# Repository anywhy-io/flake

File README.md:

<div align="center">
    
    <h3>Anywhy Flake</h3>
    <p><i>be productive, stay healthy and enjoy the process.</i></p>
</div>

# Why

By the 19th century, a need for a faster way of writing had emerged, which led to the invention of typewriters. Two centuries later, modern keyboards don't look much different from their predecessors, even though such design has been proven to be quite inefficient and often harmful.

Addressing these problems leads to huge benefits considering how often people use keyboards in the modern world.

# How

## Split

Regular keyboards are made in a single monolithic block, and the main problem is that such a form factor requires our forearms to meet in the center. To compensate for this, wrists are bent apart. This position creates an unnatural angle between the forearm and the wrist, which in the long term will likely lead to constant wrist pain.

Each half of the split keyboard can be rotated and placed in any suitable way so everyone can adapt the setup to their personal preference, avoiding potential damage to the wrists. As a bonus, we get free space right between the halves which can be occupied by a trackpad, coffee, or even a cat =^..^=

## Stagger

If you take your hand and look at the fingers, you can notice that they are positioned horizontally. Now take a look at your keyboard - the keys are grouped in arrays that are shifted vertically, known as row-based stagger.

This well-known layout forces your fingers to move in a counterintuitive way. The solution to that problem is simple: we need to rearrange the keys in a more human-friendly way.

As you can see, Flake has what's called a column-based stagger. Because of this, keys are located in the path of natural finger movement, which results in a much more pleasant typing experience and reduced fatigue.

## Key switches

There are a huge amount of various keyboard switches with different feel, size, sound, height and so on. Such variety is awesome, but the problem arrives when you have to chose one.

To address this issue, Flake utilizes hot-swap sockets. There are two different sockets per key, allowing you to use any Cherry MX and low-profile Kailh Choc switches. This way, you can always experiment with the look and feel of the keyboard and change it according to your mood.

## Keys amount

There's a high chance that some might feel confused seeing such a small number of keys, considering user productivity is one of the priorities for Anywhy.

Indeed, Flake has fewer keys than most conventional keyboards, and that's not a compromise, but a feature. A large number of keys causes hands to move around to reach further-placed keys.

Having fewer keys doesn't mean less functionality. In fact, Flake is not only fully input-compatible with regular keyboards but also allows you to add more keys than most keyboards have. All thanks to [ZMK Firmware](https://zmk.dev) and its features such as [layers](https://zmk.dev/docs/keymaps#layers).

### Flake L

There's a Flake L with 58 keys for those who aren't ready to jump down the rabbit hole yet or just prefer more keys.

### Flake S

For people who strive for absolute comfort and compactness, there is also Flake S with 40 keys.

## Thickness

The keyboard has been designed to be as thin as possible while maintaining a sturdy construction.

The keyboard body is only ~0.8 cm (without feet), which combined with the low-profile switches and caps, greatly enhances comfort.

# What

Flake supports both wired and wireless (Bluetooth) connection, which makes it perfect for both home usage with a PC or portable setup with a laptop, tablet, or even smartphone.

To achieve both types of connectivity, each half has two USB-C ports, one on the top and one on the inner side. The side port is used to connect the halves together, and then one of them (usually the left one) can be connected to any device using the top port, which is also used to charge the keyboard.

> Ports on the side are used only to communicate with each other, so they can't be used to charge the keyboard or to flash the new firmware

The keyboard allows for a maximum battery capacity of 200mah. On a single charge, the left half will last ~1 month and the right half will last over 4 months when used for 6 hours every day.

> The calculations are done with the nice!nano controller.

In order to use MX Switches, the special "plate" comes with the Flake which should be placed between the board and the switches.

# Build

If you want to build the keyboard yourself, check out [Guide](./docs/build_guide.md), which describes everything you need to build your own Flake. 

Also, make sure to check out the [Gallery ✨](./docs/gallery.md) with awesome Flake builds.

# Credits

Huge thanks to:

- [@foostan](https://github.com/foostan), the author of [Corne Keyboard](https://github.com/foostan/crkbd) which was my introduction to the world of ergonomic keyboards.
  
- [@pashutk](https://github.com/pashutk), the author of [Chocofi](https://github.com/pashutk/chocofi), an amazing tiny keyboard I've been using for a while.
  
- [@ebastler](https://github.com/ebastler/) for his amazing [marbastlib](https://github.com/ebastler/marbastlib) which is being used as the basis for footprint switches

- [@josefadamcik](https://github.com/josefadamcik), the author of [Sofle](https://github.com/josefadamcik/SofleKeyboard) which gave huge inspiration for the Flake's key layout.
  
- [@petejohanson](https://github.com/petejohanson) for creating [ZMK Firmware](https://github.com/zmkfirmware/zmk) and all the [contributors](https://github.com/zmkfirmware/zmk/graphs/contributors) that make it better each day.

- Everyone working on [KiCad](https://gitlab.com/kicad/code/kicad) and [FreeCAD](https://github.com/FreeCAD/FreeCAD), for creating such powerful open source tools

- People from the [ZMK discord server](https://zmk.dev/community/discord/invite) for being so kind while helping me learn how to design PCB and how to debug and solve various problems.

- Finally, thank you to everyone who explores unpopular technologies, digs into niche topics, and makes amazing things possible.

## Stars

Your stars give motivation to keep improving the project :)

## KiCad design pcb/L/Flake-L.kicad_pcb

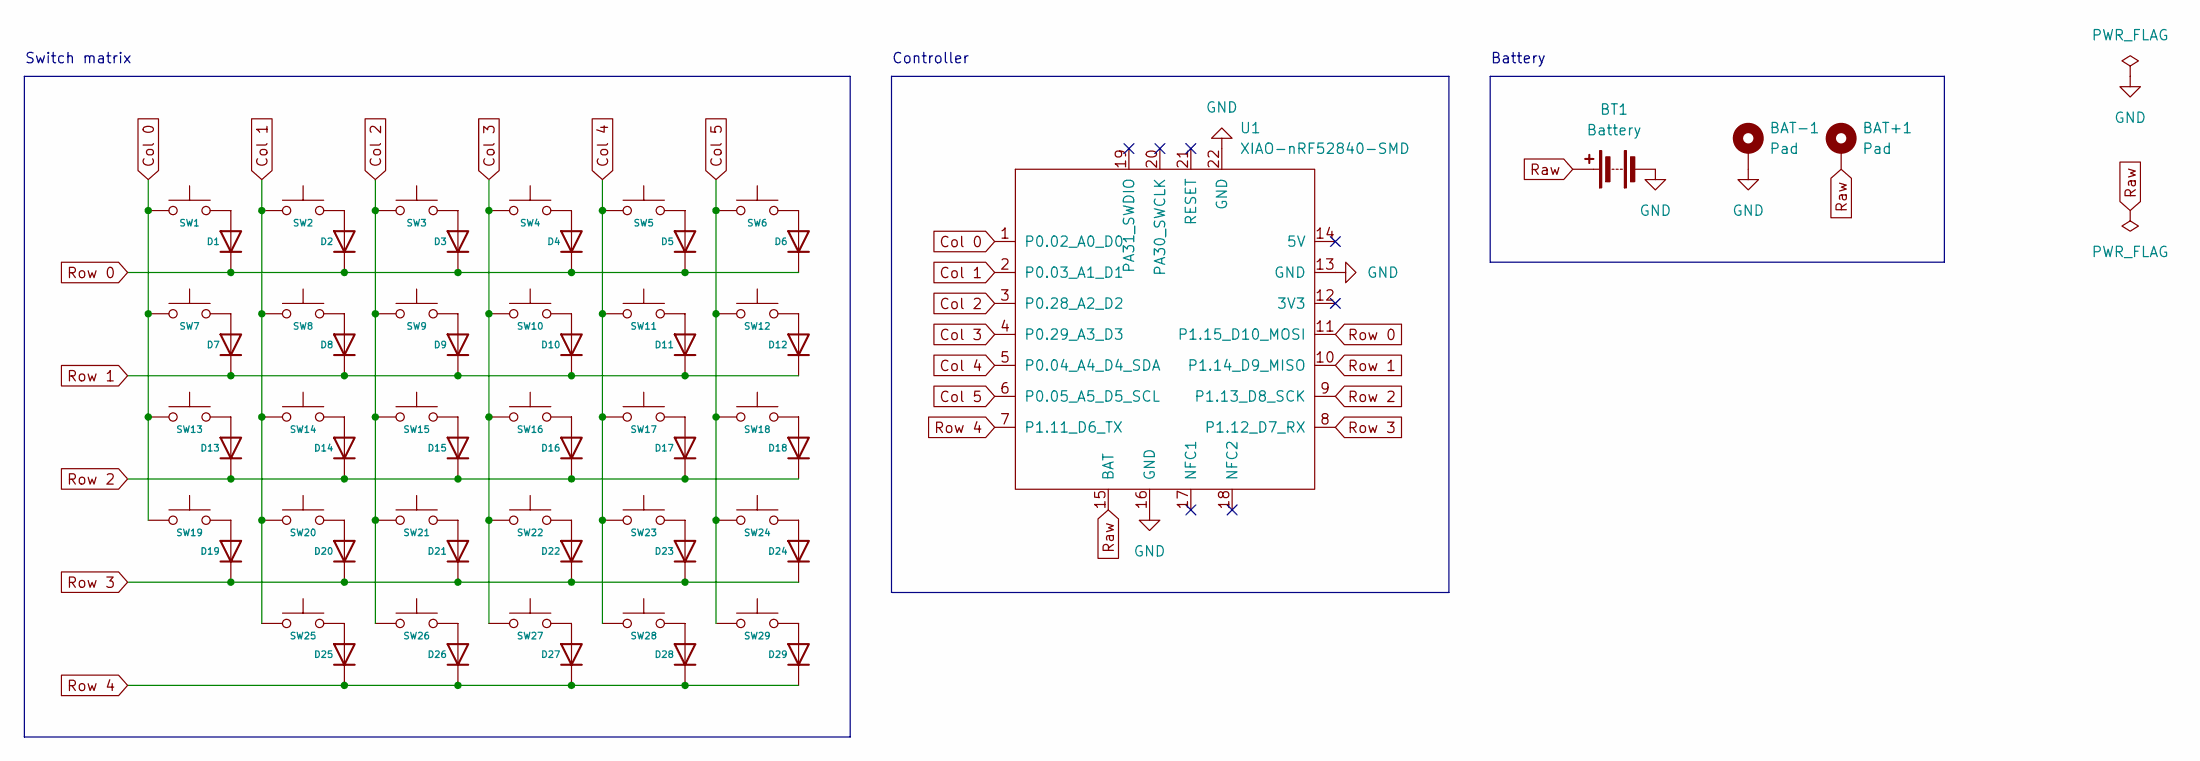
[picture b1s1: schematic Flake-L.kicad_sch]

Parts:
BAT+1: Pad
BAT-1: Pad
BT1: Battery; JST_1.25mm_Reversible
D1, D2, D3, D4, D5, D6, D7, D8, D9, D10, D11, D12, D13, D14, D15, D16, D17, D18, D19, D20, D21, D22, D23, D24, D25, D26, D27, D28, D29: D; D_SOD-123_HandSoldering_Reversible
SW1, SW2, SW3, SW4, SW5, SW6, SW7, SW8, SW9, SW10, SW11, SW12, SW13, SW14, SW15, SW16, SW17, SW18, SW19, SW20, SW21, SW22, SW23, SW24, SW25, SW26, SW27, SW28, SW29: SW_Push; SW_MX_Choc_Hotswap_Reversible
U1: XIAO-nRF52840-SMD

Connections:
Col 0: SW1.1, SW7.1, SW13.1, SW19.1, U1.1 (P0.02_A0_D0)
Col 1: SW2.1, SW8.1, SW14.1, SW20.1, SW25.1, U1.2 (P0.03_A1_D1)
Col 2: SW3.1, SW9.1, SW15.1, SW21.1, SW26.1, U1.3 (P0.28_A2_D2)
Col 3: SW4.1, SW10.1, SW16.1, SW22.1, SW27.1, U1.4 (P0.29_A3_D3)
Col 4: SW5.1, SW11.1, SW17.1, SW23.1, SW28.1, U1.5 (P0.04_A4_D4_SDA)
Col 5: SW6.1, SW12.1, SW18.1, SW24.1, SW29.1, U1.6 (P0.05_A5_D5_SCL)
GND: BAT-1.1, BT1.2 (-), U1.13 (GND), U1.16 (GND), U1.22 (GND)
unnamed: D1.2 (A), SW1.2
unnamed: D2.2 (A), SW2.2
unnamed: D3.2 (A), SW3.2
unnamed: D4.2 (A), SW4.2
unnamed: D5.2 (A), SW5.2
unnamed: D6.2 (A), SW6.2
unnamed: D7.2 (A), SW7.2
unnamed: D8.2 (A), SW8.2
unnamed: D9.2 (A), SW9.2
unnamed: D10.2 (A), SW10.2
unnamed: D11.2 (A), SW11.2
unnamed: D12.2 (A), SW12.2
unnamed: D13.2 (A), SW13.2
unnamed: D14.2 (A), SW14.2
unnamed: D15.2 (A), SW15.2
unnamed: D16.2 (A), SW16.2
unnamed: D17.2 (A), SW17.2
unnamed: D18.2 (A), SW18.2
unnamed: D19.2 (A), SW19.2
unnamed: D20.2 (A), SW20.2
unnamed: D21.2 (A), SW21.2
unnamed: D22.2 (A), SW22.2
unnamed: D23.2 (A), SW23.2
unnamed: D24.2 (A), SW24.2
unnamed: D25.2 (A), SW25.2
unnamed: D26.2 (A), SW26.2
unnamed: D27.2 (A), SW27.2
unnamed: D28.2 (A), SW28.2
unnamed: D29.2 (A), SW29.2
Raw: BAT+1.1, BT1.1 (+), U1.15 (BAT)
Row 0: D1.1 (K), D2.1 (K), D3.1 (K), D4.1 (K), D5.1 (K), D6.1 (K), U1.11 (P1.15_D10_MOSI)
Row 1: D7.1 (K), D8.1 (K), D9.1 (K), D10.1 (K), D11.1 (K), D12.1 (K), U1.10 (P1.14_D9_MISO)
Row 2: D13.1 (K), D14.1 (K), D15.1 (K), D16.1 (K), D17.1 (K), D18.1 (K), U1.9 (P1.13_D8_SCK)
Row 3: D19.1 (K), D20.1 (K), D21.1 (K), D22.1 (K), D23.1 (K), D24.1 (K), U1.8 (P1.12_D7_RX)
Row 4: D25.1 (K), D26.1 (K), D27.1 (K), D28.1 (K), D29.1 (K), U1.7 (P1.11_D6_TX)

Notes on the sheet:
Switch matrix
Controller
Battery

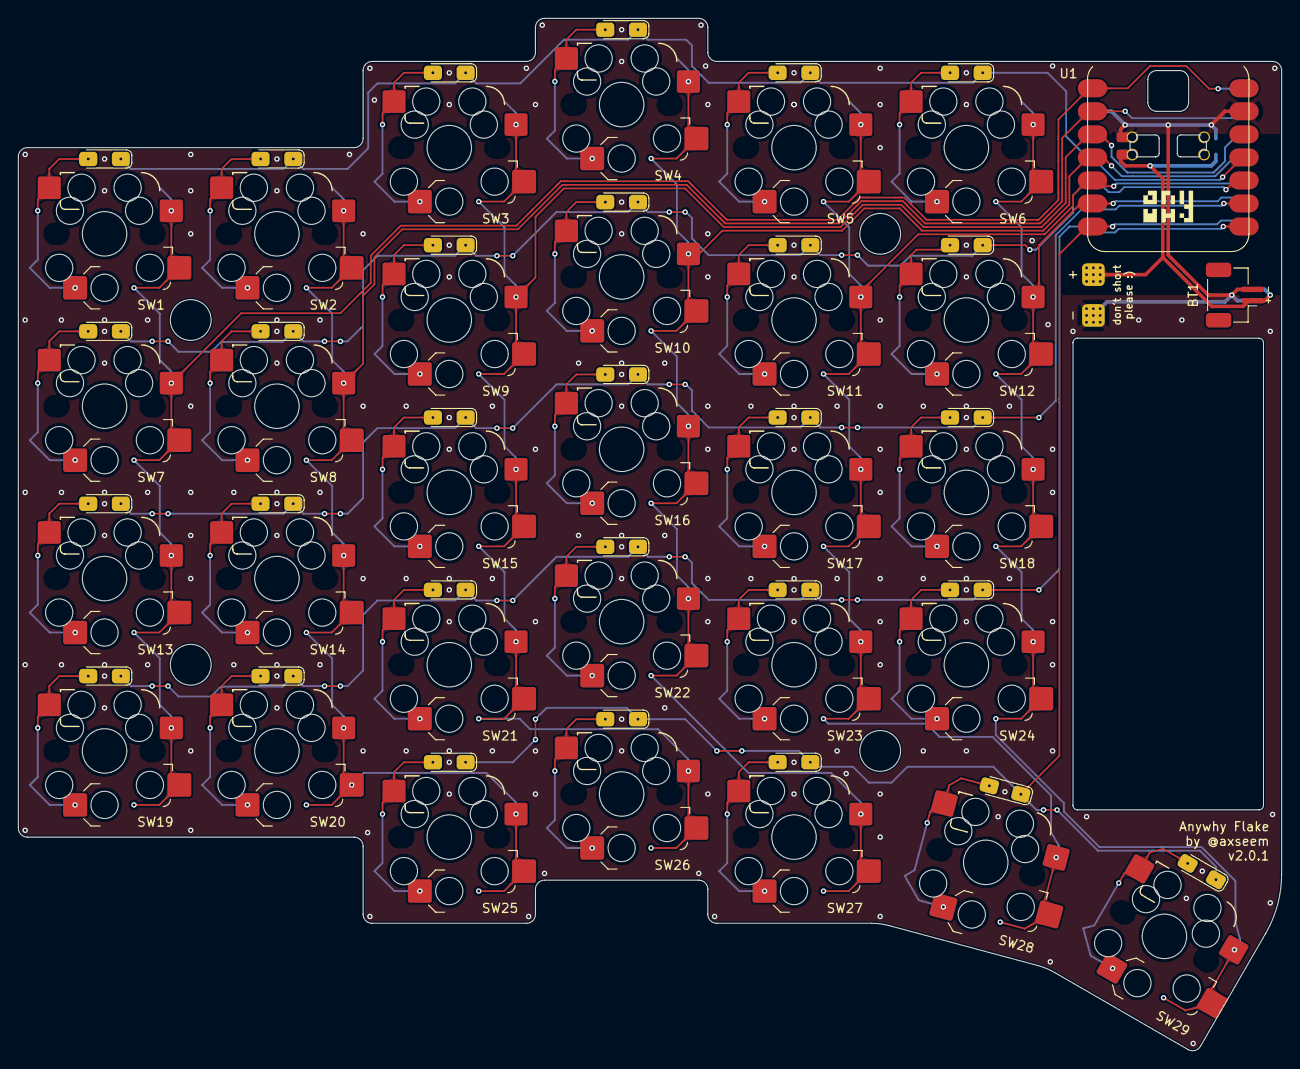
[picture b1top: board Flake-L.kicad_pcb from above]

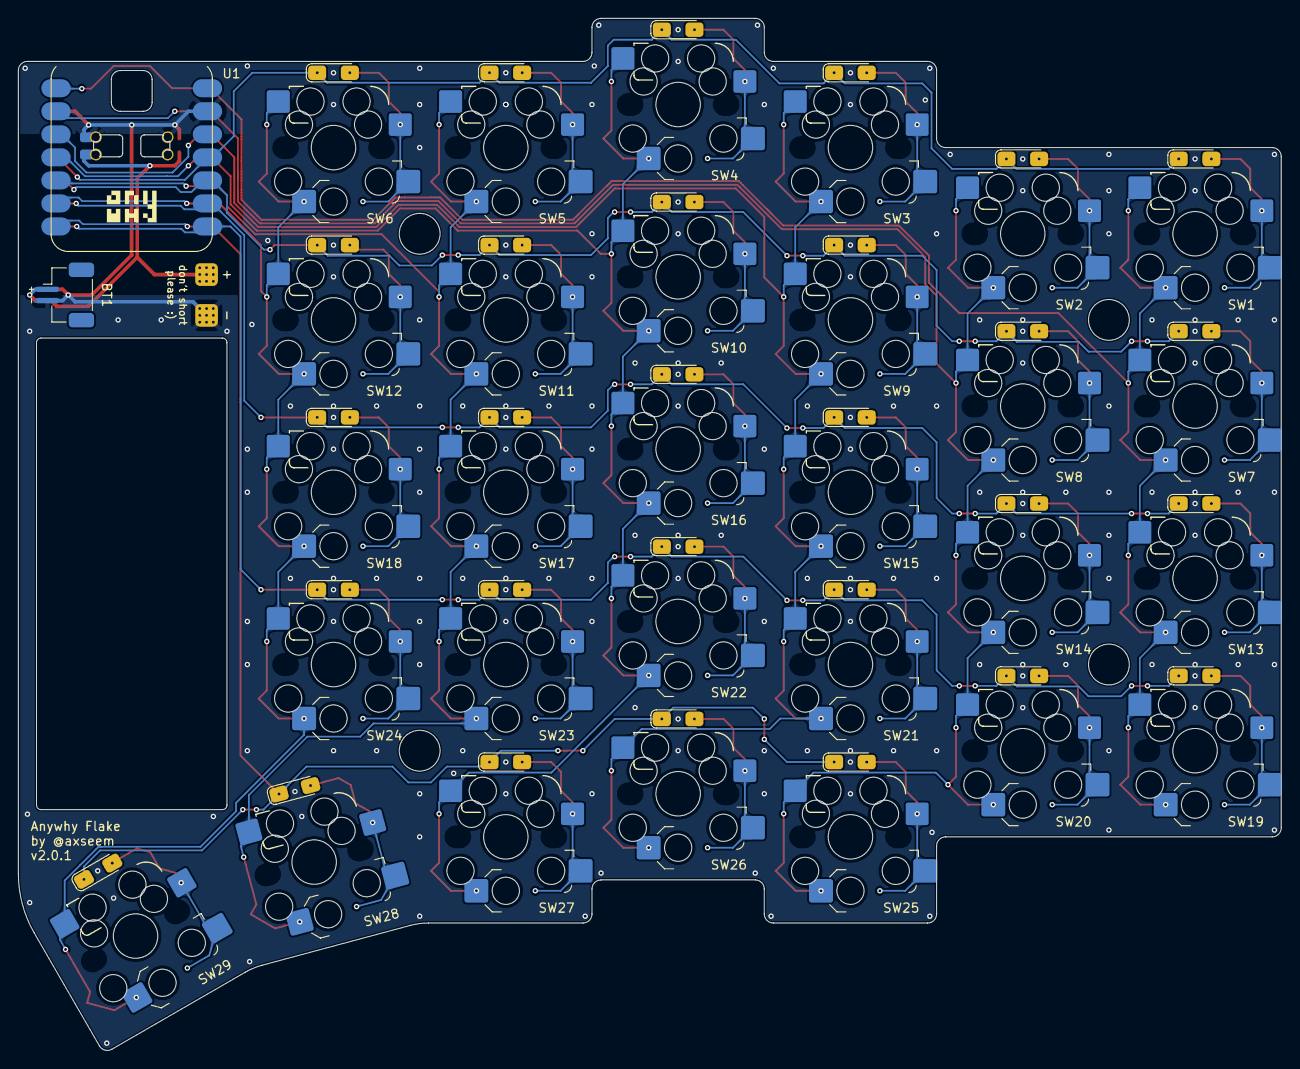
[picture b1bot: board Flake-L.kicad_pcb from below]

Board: 2 copper layers, 139.2 x 113.8 mm, 62 parts (33 on the bottom side), 42 nets.

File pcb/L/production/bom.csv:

Designator,Footprint,Quantity,Value,LCSC Part #
"BAT+1, BAT-1",Pad,2,Pad,
BT1,JST_1.25mm_Reversible,1,Battery,
"D1, D10, D11, D12, D13, D14, D15, D16, D17, D18, D19, D2, D20, D21, D22, D23, D24, D25, D26, D27, D28, D29, D3, D4, D5, D6, D7, D8, D9",D_SOD-123_HandSoldering_Reversible,29,D,
"SW1, SW10, SW11, SW12, SW13, SW14, SW15, SW16, SW17, SW18, SW19, SW2, SW20, SW21, SW22, SW23, SW24, SW25, SW26, SW27, SW28, SW29, SW3, SW4, SW5, SW6, SW7, SW8, SW9",SW_MX_Choc_Hotswap_Reversible,29,SW_Push,
U1,XIAO-nRF52840-SMD,1,XIAO-nRF52840-SMD,

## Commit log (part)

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2025-01-11 v1.0
2025-01-11 pcb: remove unused footprints
2025-01-12 docs: add build guide
2025-01-12 docs: fix Flake L greber link
2025-01-12 docs: fix typo
2025-01-13 enclosure: plates: remove surface above controller
2025-01-13 enclosure: fix topology
2025-01-26 docs: update config image
2025-01-27 docs: add star-history
2025-01-28 docs: add gallery page
2025-02-02 gallery: add build by @devpew
2025-02-06 enclosure: split into individual files
2025-02-06 gallery: add build by u/kurisutofujp
2025-02-13 readme: change star-history chart type
2025-02-27 gallery: add build by u/caiodelgado
2025-03-03 gallery: update caiodelgado's photos
2025-03-03 gallery: update alt text
2025-03-22 gallery: add build by @peppapighs
2025-09-20 Flake v2
2025-09-20 chore: fix PCB path
2025-09-20 chore: delete extra readme
2025-09-20 docs: only horizontal jst!
2025-09-21 docs: add usb image
2025-09-25 fix(enclosure): path typo
2025-09-25 feat(enclosure): no chamfer version for easier print
2025-10-15 docs: Flake L supports 502050 battery
2025-10-17 fix(build_guide): screws are 4mm long
2025-11-02 fix(build_guide): update screw size from M2x8mm to M2x4mm in the instructions
2026-01-07 gallery: add build by u/Constant_Pin_7757
2026-02-15 Add some hints and a troubleshooting section to build guide
2026-02-18 Add a operational check section
2026-03-09 fix: top enclosure resize breaks the model
2026-03-09 fix: top enclosure resize breaks the model (#17)
